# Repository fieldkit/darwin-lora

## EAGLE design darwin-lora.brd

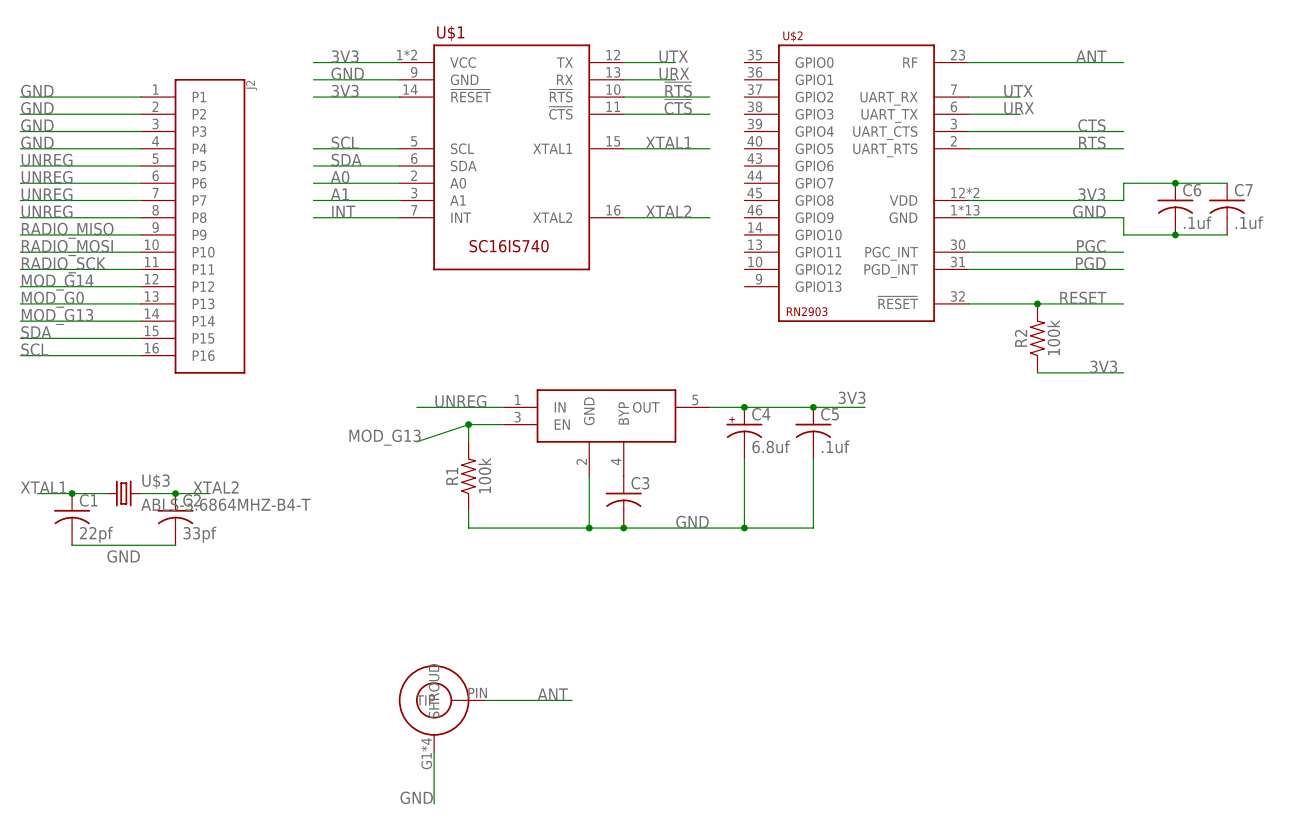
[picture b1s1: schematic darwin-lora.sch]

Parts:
C1: 22pf; C0603K
C2: 33pf; C0603K
C3: C-USC0603K; C0603K
C4: 6.8uf; A/3216-18R
C5, C6, C7: .1uf; C0603K
J2: 505110-1692
R1, R2: 100k; 0603
U$1: SC16IS740; SOP65P640X110-16
U$2: RN2903
U$3: ABLS-3.6864MHZ-B4-T; ABLS
U$4: MIC5219-3.3YM5-TR; SOT95P280X145-5
U$5: 5-1814832-1

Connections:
3V3: C4.+, C5.1, C6.1, C7.1, R2.1, U$1.1 (VCC), U$1.8 (VCC), U$1.14 (!RESET), U$2.12 (VDD), U$2.34 (VDD), U$4.5 (OUT)
!CTS: U$1.11 (!CTS)
!RTS: U$1.10 (!RTS)
A0: U$1.2 (A0)
A1: U$1.3 (A1)
ANT: U$2.23 (RF), U$5.PIN (TIP)
CTS: U$2.3 (UART_CTS)
GND: C1.2, C2.2, C3.2, C4.-, C5.2, C6.2, C7.2, J2.1, J2.2, J2.3, J2.4, R1.1, U$1.9 (GND), U$2.1 (GND), U$2.8 (GND), U$2.11 (GND), U$2.20 (GND), U$2.21 (GND), U$2.22 (GND), U$2.24 (GND), U$2.26 (GND), U$2.27 (GND), U$2.28 (GND), U$2.33 (GND), U$2.41 (GND), U$2.47 (GND), U$4.2 (GND), U$5.G1 (SHROUD), U$5.G2 (SHROUD), U$5.G3 (SHROUD), U$5.G4 (SHROUD)
INT: U$1.7 (INT)
MOD_G0: J2.13
MOD_G13: J2.14, R1.2, U$4.3 (EN)
MOD_G14: J2.12
unnamed: C3.1, U$4.4 (BYP)
PGC: U$2.30 (PGC_INT)
PGD: U$2.31 (PGD_INT)
RADIO_MISO: J2.9
RADIO_MOSI: J2.10
RADIO_SCK: J2.11
RESET: R2.2, U$2.32 (!RESET)
RTS: U$2.2 (UART_RTS)
SCL: J2.16, U$1.5 (SCL)
SDA: J2.15, U$1.6 (SDA)
UNREG: J2.5, J2.6, J2.7, J2.8, U$4.1 (IN)
URX: U$1.13 (RX), U$2.6 (UART_TX)
UTX: U$1.12 (TX), U$2.7 (UART_RX)
XTAL1: C1.1, U$1.15 (XTAL1), U$3.P$1 (1)
XTAL2: C2.1, U$1.16 (XTAL2), U$3.P$2 (2)

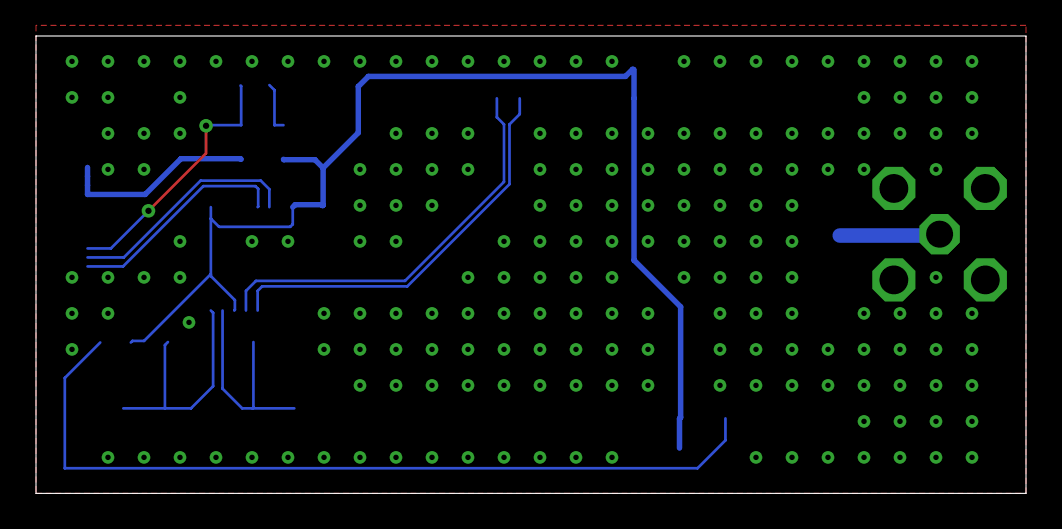
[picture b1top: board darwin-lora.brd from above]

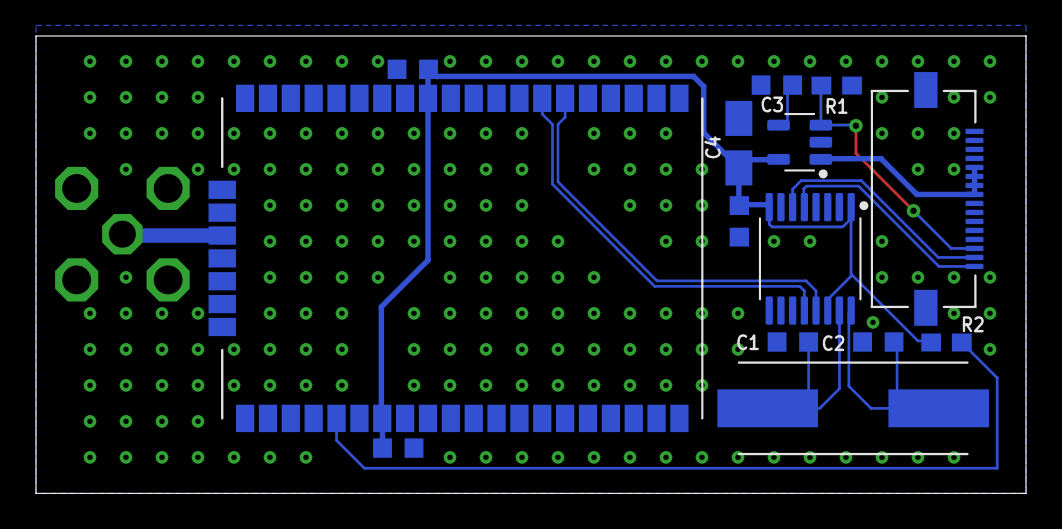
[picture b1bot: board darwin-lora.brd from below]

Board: 2 copper layers, 55.0 x 25.4 mm, 15 parts (14 on the bottom side), 13 nets.

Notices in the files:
parts and their libraries:
SparkFun-Resistors: Licensing: Creative Commons ShareAlike 4.0 International - https://creativecommons.org/licenses/by-sa/4.0
